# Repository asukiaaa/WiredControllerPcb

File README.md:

# WiredControllerPcb

A wired controller that communicate in I2C with using [a library](https://github.com/asukiaaa/WiredController_asukiaaa).

# License

MIT

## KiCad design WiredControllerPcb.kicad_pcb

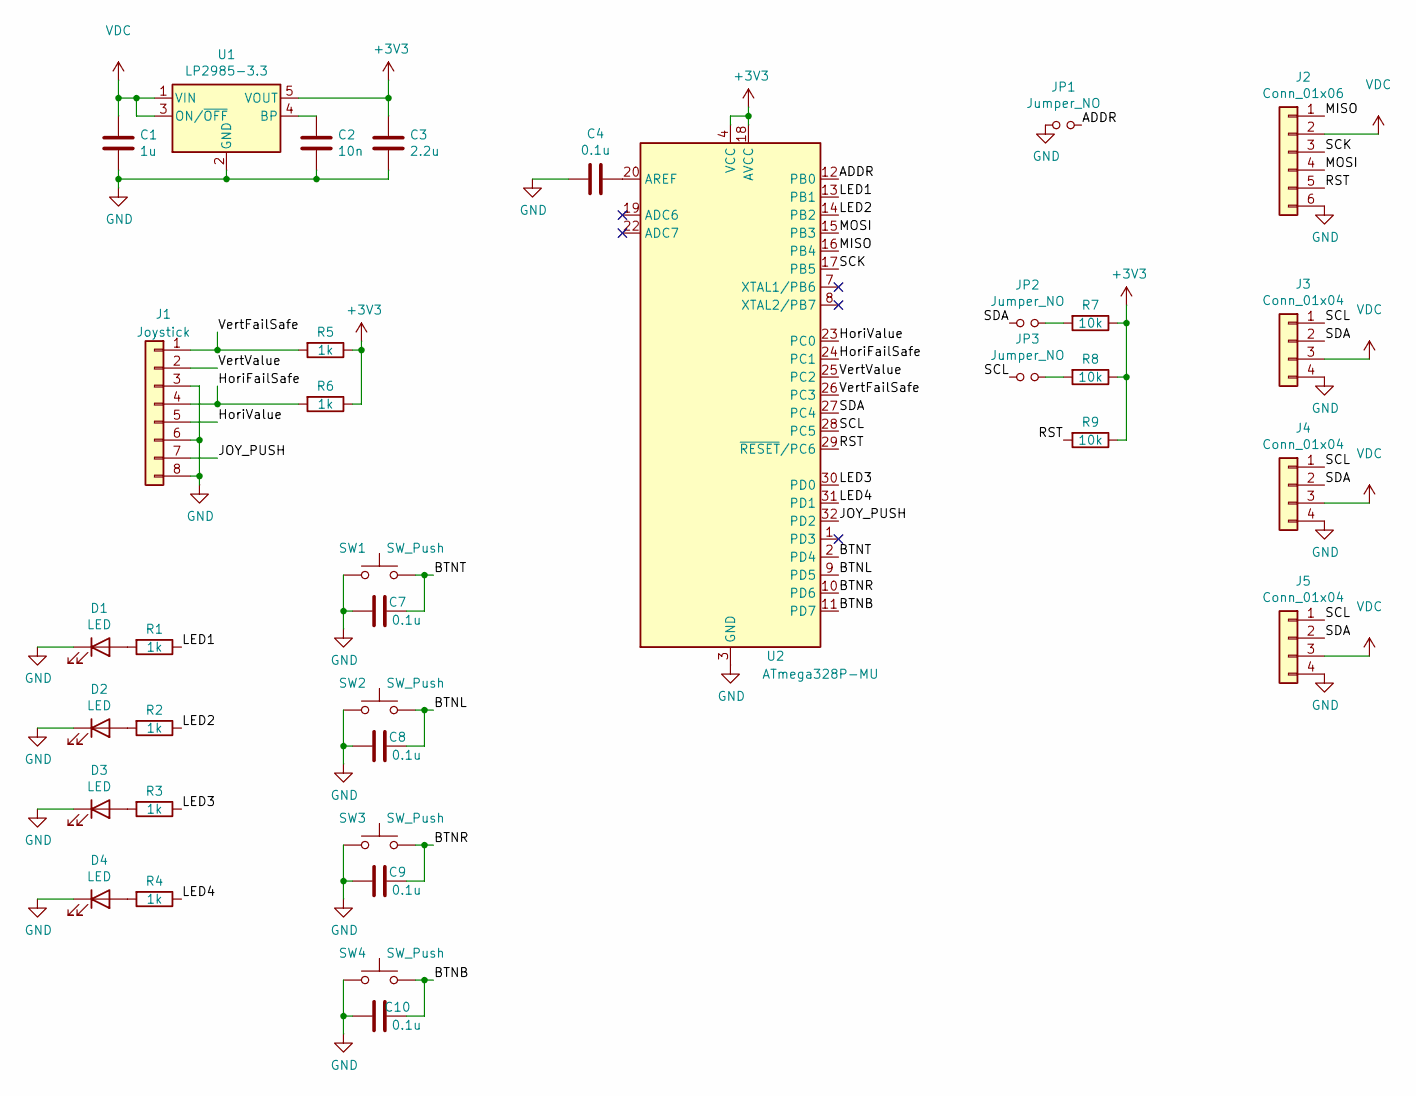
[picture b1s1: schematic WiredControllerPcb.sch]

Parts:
C1: 1u; C_0603_1608Metric
C2: 10n; C_0603_1608Metric
C3: 2.2u; C_0603_1608Metric
C4, C7, C8, C9, C10: 0.1u; C_0603_1608Metric
D1, D2, D3, D4: LED; LED_0603_1608Metric
J1: Joystick; PS4tJoystick
J2: Conn_01x06; 2x03_P2.54mm_Pads
J3: Conn_01x04; NS-Tech_Grove_1x04_P2mm_Horizontal
J4: Conn_01x04; TerminalBlock_bornier-4_P5.08mm
J5: Conn_01x04; PinHeader_1x04_P2.54mm_Vertical
JP1, JP2, JP3: Jumper_NO; SolderJumper-2_P1.3mm_Open_RoundedPad1.0x1.5mm
R1, R2, R3, R4, R5, R6: 1k; R_0603_1608Metric
R7, R8, R9: 10k; R_0603_1608Metric
SW1, SW2, SW3, SW4: SW_Push; SW_Center_PUSH-12mm
U1: LP2985-3.3; SOT-23-5
U2: ATmega328P-MU; QFN-32-1EP_5x5mm_P0.5mm_EP3.1x3.1mm

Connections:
+3V3: C3.1, R5.1, R6.1, R7.1, R8.1, R9.1, U1.5 (VOUT), U2.4 (VCC), U2.6 (VCC), U2.18 (AVCC)
/ADDR: JP1.2, U2.12 (PB0)
/BTNB: C10.1, SW4.2, U2.11 (PD7)
/BTNL: C8.1, SW2.2, U2.9 (PD5)
/BTNR: C9.1, SW3.2, U2.10 (PD6)
/BTNT: C7.1, SW1.2, U2.2 (PD4)
/HoriFailSafe: J1.4, R6.2, U2.24 (PC1)
/HoriValue: J1.5, U2.23 (PC0)
/JOY_PUSH: J1.7, U2.32 (PD2)
/LED1: R1.1, U2.13 (PB1)
/LED2: R2.1, U2.14 (PB2)
/LED3: R3.1, U2.30 (PD0)
/LED4: R4.1, U2.31 (PD1)
/MISO: J2.1, U2.16 (PB4)
/MOSI: J2.4, U2.15 (PB3)
/RST: J2.5, R9.2, U2.29 (~RESET~/PC6)
/SCK: J2.3, U2.17 (PB5)
/SCL: J3.1, J4.1, J5.1, JP3.1, U2.28 (PC5)
/SDA: J3.2, J4.2, J5.2, JP2.1, U2.27 (PC4)
/VertFailSafe: J1.1, R5.2, U2.26 (PC3)
/VertValue: J1.2, U2.25 (PC2)
GND: C1.2, C2.2, C3.2, C4.1, C7.2, C8.2, C9.2, C10.2, D1.1 (K), D2.1 (K), D3.1 (K), D4.1 (K), J1.3, J1.6, J1.8, J2.6, J3.4, J4.4, J5.4, JP1.1, SW1.1, SW2.1, SW3.1, SW4.1, U1.2 (GND), U2.3 (GND), U2.5 (GND), U2.21 (GND), U2.33 (GND)
unnamed: C2.1, U1.4 (BP)
unnamed: C4.2, U2.20 (AREF)
unnamed: D1.2 (A), R1.2
unnamed: D2.2 (A), R2.2
unnamed: D3.2 (A), R3.2
unnamed: D4.2 (A), R4.2
unnamed: JP2.2, R7.2
unnamed: JP3.2, R8.2
VDC: C1.1, J2.2, J3.3, J4.3, J5.3, U1.1 (VIN), U1.3 (ON/~OFF~)

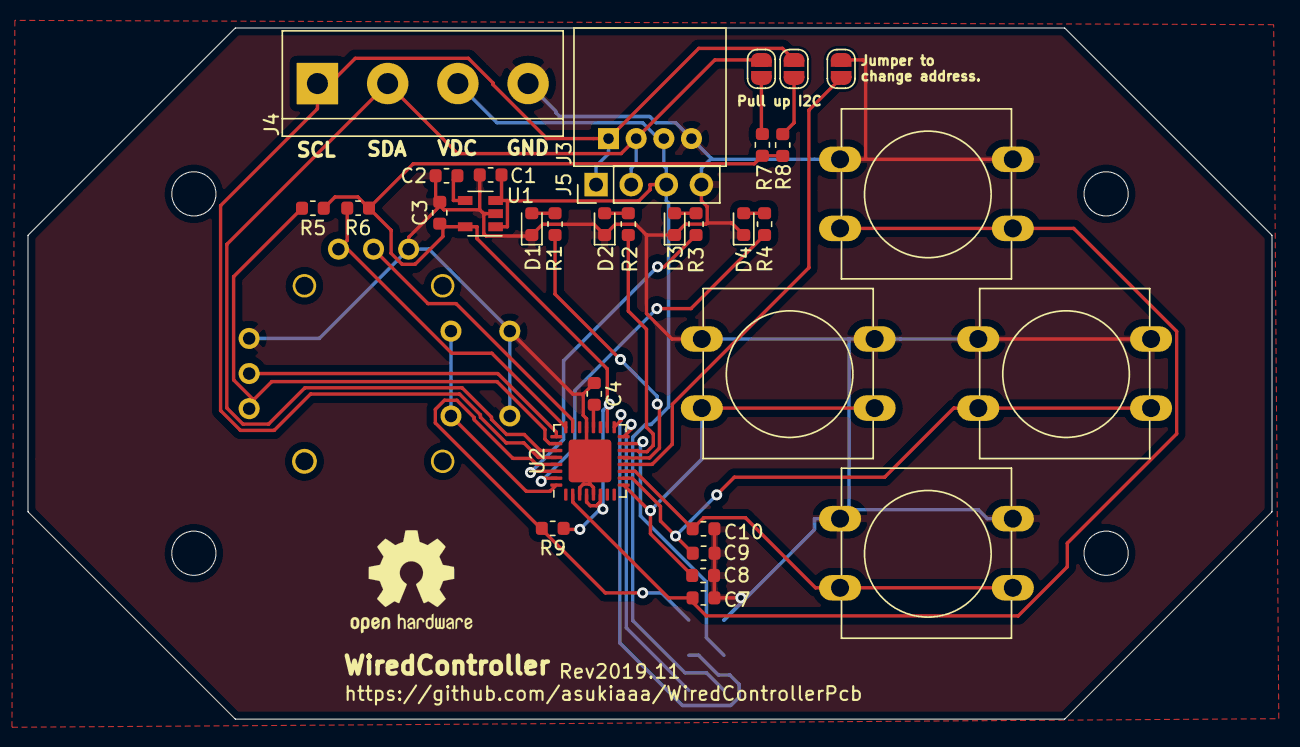
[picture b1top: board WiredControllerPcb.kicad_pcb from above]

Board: 2 copper layers, 90.0 x 50.0 mm, 39 parts (1 on the bottom side), 31 nets.

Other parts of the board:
REF1, REF2, REF3, REF4: MountingHole_3.2mm_M3

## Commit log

2019-08-25 Add plate
2019-09-01 Correct silk position of MOSI and GND
2019-09-01 Correct pin assign for LED4
2019-09-01 Update symbol key for R4 ~ R6
2019-09-02 Apply 2x03 pads for 6pins
2019-09-02 Add sch-bak to gitignore
2019-09-05 Update crystal for bom and schema
2019-09-05 Update connector on bom
2019-09-10 Remove uart connector and use 0 and 1 to LEDs
2019-09-15 Update hole position of PS4Joystick
2019-09-15 Remove crystal, change leds and replace miso and mosi
2019-09-15 Repalce VCC to VCD
2019-09-16 Add pull up resistors and jumpers for sda and scl
2019-09-17 Add terminal block
2019-09-20 Add pin header
2019-09-21 Add gerber_to_order directory to .gitignore
2019-09-24 Remove un used component from bom for fusionPCB
2019-09-24 Add bom for elecrow
2019-09-29 Specify color of led on bom for elecrow
2019-09-29 Add pcb requirement
2019-09-30 Change resister to pullup to 10k from 1k
2019-10-01 Remove wrong MPN for 10k resister on bom for elecrow
2019-11-12 Correct connection ADDR and GND
2019-11-17 Correct position of right button and bottom button
2019-11-28 Add links to readme
2020-02-09 Add pull up resistor to reset pin
2022-06-27 Update for KiCad6
